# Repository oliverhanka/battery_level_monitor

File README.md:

# Battery level monitor
The board is designed to measure the battery level (voltage) with an uC's ADC. The on-board voltage divider must be parameterized (R1 and R2) according to the uC's max ADC input as well as the battery's voltage level. The battery voltage may be higher then the ADC's Vcc.

The circuit includes two MOSFETs to cut-off the voltage divider in order to not drain the battery when not in use. The uC must pull up EN to activate the voltage divider. If EN is left floating (e.g., the uC is turned off or in deep-sleep), the on-board pulldown resistor cuts of the voltage divider.

## Parameterize voltage divider
Calculate the two resistors R1 and R2 to fit your application needs (e.g., use an [online calculator](http://www.ohmslawcalculator.com/voltage-divider-calculator)). Example:

| Battery | ADC input | R1 | R1 |
| -------- | -------- | -------- | -------- |
| 14V     | 3.3V     | 75k     | 18k |

(resistor values adjusted to match common resistor series)

## Connectors / headers / solder jumper

| Connector | Purpose |
| -------- | -------- |
| J1     | to uC - (1) EN, (2) ADC, (3) GND |
| J2     | to battery - (1) Vbat, (2) GND |
| JP1    | bridge to enable voltage divider permanetly |

## Build

The board is hand solderable with some practise. Components are 0805 and SOT23 footprint.

### Schematic

### Bill of materials (BOM)

| Designator | Manufacturer Part Number | Qty |
| -------- | -------- |	-------- |	
|J1 |	S3B-PH-SM4-TB(LF)(SN) |	1 |
|J2 |	S2B-PH-SM4-TB(LF)(SN) |	1 |
|R1 |	(must be calculated) 0805 |	1 |
|R2 |	(must be calculated) 0805 |	1 |
|R3 |	100k 0805|	1 |
|R4 |	10k 0805|	1 |
|C1 |	100nF 0805|	1 |
|Q1 |	BSS84 SOT23|	1 |
|Q2 |	BSS123 SOT23 |	1 |

### PCB Rendering
 | 
------------ | -------------
frontside rev 1.0 | backside rev 1.0

### Order PCBs
You can create gerber files (KiCad -> Plot) and upload them to the PCB manufacturer of your choice. You can also use this preconfigured [PCBs.io link](https://PCBs.io/share/4o5we) which will earn me some royalties.

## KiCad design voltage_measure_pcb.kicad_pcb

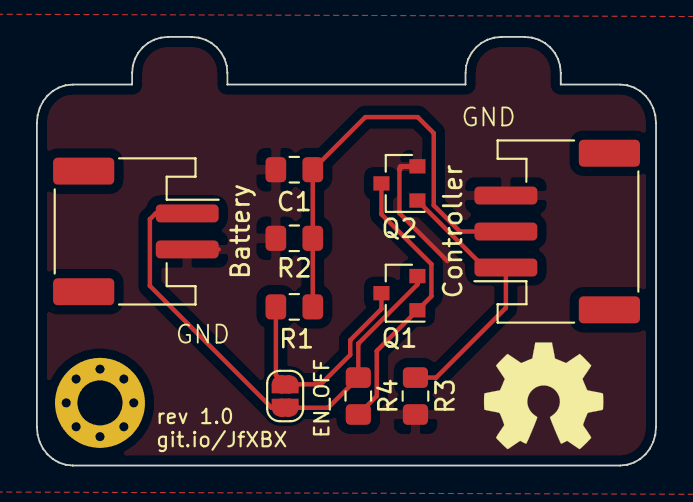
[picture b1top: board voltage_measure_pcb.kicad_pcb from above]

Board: 2 copper layers, 34.4 x 23.8 mm, 10 parts (0 on the bottom side), 6 nets.

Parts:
Battery: Conn_01x02_Male; JST_PH_S2B-PH-SM4-TB_1x02-1MP_P2.00mm_Horizontal
C1: 100nF; C_0805_2012Metric_Pad1.15x1.40mm_HandSolder
Controller: Conn_01x03_Male; JST_PH_S3B-PH-SM4-TB_1x03-1MP_P2.00mm_Horizontal
EN_OFF: SolderJumper_2_Open; SolderJumper-2_P1.3mm_Open_RoundedPad1.0x1.5mm
Q1: BSS84; SOT-23
Q2: BSS123; SOT-23
R1, R2: R; R_0805_2012Metric_Pad1.15x1.40mm_HandSolder
R3: 100k; R_0805_2012Metric_Pad1.15x1.40mm_HandSolder
R4: 10k; R_0805_2012Metric_Pad1.15x1.40mm_HandSolder

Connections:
+BATT: Battery.1, EN_OFF.1, Q1.2, R4.1
/ADC: C1.1, Controller.2, R1.2, R2.1
/EN: Controller.1, Q2.1, R3.1
GND: Battery.2, C1.2, Controller.3, Q2.2, R2.2, R3.2
unnamed: EN_OFF.2, Q1.3, R1.1
unnamed: Q1.1, Q2.3, R4.2

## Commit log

2020-06-04 initial commit - rev 1.0
2020-06-04 missing EN wire fixed
